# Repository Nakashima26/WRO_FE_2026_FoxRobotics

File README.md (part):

# WRO 2026 — Future Engineers | Self-Driving Car

> **Team:** FoxRobotics
> **| Members:** Erick Blanco · Jesse Banda · César Emiliano Ahumada
> **| Coach:** Daniel Millan
> **| Country / Region:** México — Baja California
> **| Season:** 2026

---

## Table of Contents

1. [Vehicle Overview](#1-vehicle-overview)
   - [1.1 Design goals](#11-design-goals) · [1.2 Bill of Materials](#12-bill-of-materials) · [1.3 What changed in v2](#13-what-changed-for-the-international-final-v2)
2. [Mechanical Design & Mobility](#2-mechanical-design--mobility)
   - [2.1 Chassis selection](#21-chassis-selection) · [2.2 Wheels](#22-wheels) · [2.3 Drive system (torque vs. speed)](#23-drive-system-torque-vs-speed-analysis) · [2.4 Steering](#24-steering--rack-and-pinion-with-ackermann-geometry) · [2.5 Custom parts & assembly](#25-custom-parts--assembly) · [2.6 v2 chassis](#26-v2-chassis--shorter-car-pi-on-top)
3. [Power Architecture & Sensors](#3-power-architecture--sensors)
   - [3.1 Power budget](#31-power-budget) · [3.2 Sensor selection and placement](#32-sensor-selection-and-placement) · [3.3 PCB & wiring](#33-pcb--wiring) · [3.4 Raspberry Pi 5](#34-main-computer--raspberry-pi-5-v2)
4. [Software Architecture](#4-software-architecture)
   - [4.1 System overview](#41-system-overview--two-controllers-one-link) · [4.2 Inter-controller protocol ("V2")](#42-inter-controller-protocol-v2) · [4.3 Vision pipeline](#43-vision-pipeline-raspberry-pi--pure_pursuit) · [4.4 Obstacle handling](#44-obstacle-handling-obstacle-challenge) · [4.5 ESP32 state machine](#45-esp32-finite-state-machine-srcesp32purepursuitpurepursuitino) · [4.6 Cascade PID](#46-cascade-pid-always-running-underneath) · [4.7 Startup handshake](#47-startup-handshake) · [4.8 Development status](#48-development-status) · [4.9 Route mode (v2)](#49-route-mode-v2--a-planned-route-instead-of-reactive-steering)
5. [Systemic Thinking & Engineering Decisions](#5-systemic-thinking--engineering-decisions)
   - [5.0 Design constraints](#50-design-constraints) · [5.1 Subsystem interaction map](#51-subsystem-interaction-map) · [5.2 Key engineering trade-offs](#52-key-engineering-trade-offs) · [5.3 Iteration log](#53-iteration-log) · [5.4 Risk analysis](#54-risk-analysis) · [5.5 Failure & Incident log](#55-failure--incident-log)
6. [Testing & Validation](#6-testing--validation)
   - [6.1 How we test](#61-how-we-test) · [6.2 Results to date](#62-results-to-date) · [6.3 Validation matrix](#63-validation-matrix) · [6.4 Pre-run checklist](#64-pre-run-checklist-each-venue) · [6.5 Milestones](#65-milestones) · [6.6 Releases](#66-releases)
7. [How to Build & Run](#7-how-to-build--run)
   - [7.1 Hardware](#71-hardware-requirements) · [7.2 ESP32 firmware](#72-esp32-firmware) · [7.3 Raspberry Pi software](#73-raspberry-pi-software) · [7.4 Calibration](#74-calibration-before-each-venue) · [7.5 Run](#75-run) · [7.6 Autostart & deployment](#76-autostart--deployment)
8. [Repository Structure](#8-repository-structure)
9. [Videos](#9-videos)
10. [Photos](#10-photos)

**Companion document:** [Engineering Journal](ENGINEERING_JOURNAL.md) — the dated, phase-by-phase build log, from the pre-repo design work through today, tied to commits. [§5.3 Iteration log](#53-iteration-log) and [§6.5 Milestones](#65-milestones) are the thematic views of the same history.

---

# 1. Vehicle Overview

Our vehicle is a custom-built autonomous car for the WRO 2026 Future Engineers — Self-Driving Cars challenge. It completes 3 laps around a randomized track, and in the Obstacle Challenge it also detects and correctly passes coloured traffic-sign pillars (**red → keep the pillar on the car's left / pass on its right; green → keep it on the right / pass on its left**) before parking at the end.

The car uses **two controllers working together**: a Raspberry Pi runs the camera vision pipeline (a Raspberry Pi 4 at the national final, a Raspberry Pi 5 for the international final) and the high-level path planner (Pure Pursuit), and an ESP32 runs the real-time control loop, the state machine and all the actuators. They talk over a UART link with a small line-based protocol ("V2"). This split is the central architectural decision of the project and is explained in [Section 4](#4-software-architecture) and [Section 5](#5-systemic-thinking--engineering-decisions).

**Key specifications:**

| Parameter | Value |
|---|---|
| Dimensions | v1: 210 × 140 × 80 mm body, ≈240 mm overall with the extension added to drive out of the parking lot · v2: ≈170 × 130 × 110 mm (168.7 × 128 mm in CAD; height includes the camera ribbon over the top, §2.6) |
| Weight | 564 g |
| Drive type | Rear-wheel drive (RWD) |
| Steering | Ackermann rack-and-pinion, SG90 servo — v2: 53° inner / 37° outer wheel at full lock, ~106% Ackermann (§2.4) |
| High-level controller | Raspberry Pi 5, 16 GB + Active Cooler (vision + Pure Pursuit) — Raspberry Pi 4 Model B until the national final (§3.4) |
| Real-time controller | ESP32 DevKit (FSM, PID, motor & sensor I/O) |
| Inter-controller link | UART @ 115200 baud, line protocol "V2" (see §4.2) |
| Vision | Raspberry Pi Camera, NoIR wide-angle lens (FOV ≈ 120°), processed at 640 × 480; custom lens-shading calibration on the Pi 5 (ERR-03) |
| Distance sensors | HC-SR04 (5V) × 3 — left, right, front — via 5V↔3.3V level shifter · v2: + VL53L1X ToF × 4, in integration (§3.2) |
| IMU | MPU-6050 (gyroscope + accelerometer) · v2: BNO085 with on-chip sensor fusion, in integration (§3.2) |
| Drive motor | v1: N20 DC gear motor (50:1) · v2: Pololu 50:1 12 V gear motor **with encoder** · + 2:1 stage → 100:1 total |
| Motor driver | TB6612FNG |
| Battery | 3S LiPo 11.1 V 2200 mAh |
| Logic power | MINI560 step-down, 5 V |

## 1.1 Design goals

One reliable vehicle that finishes **both** challenges — scoring for completing three laps consistently over completing them fast. Everything below follows from that.

- **Fixed architecture from day one: Raspberry Pi 4 + ESP32.** The Pi does *all* image processing and vision; the ESP32 does *all* peripheral I/O — both sensing and actuation. This split was decided before the first line of code and never revisited.
- **Small footprint for maneuverability.** Comfortably inside the rulebook envelope with ~10 cm of margin on width and length — the car is ≈ 20 × 10 cm, deliberately smaller than the limit so it has room to maneuver in the obstacle field.
- **Mechanically extensible.** The chassis and the PCB were designed so components could be added later without a redesign. This paid off directly: the front ultrasonic — added for the obstacle-round segmented turn (see [§4.5](#45-esp32-finite-state-machine-srcesp32purepursuitpurepursuitino)) — went from idea to mounted-and-wired in under 30 minutes because both the chassis and the PCB already had the space and a spare header.
- **Tight-turn capable.** Rack-and-pinion steering driving both wheels symmetrically ([§2.4](#24-steering--rack-and-pinion-with-ackermann-geometry)) so the car can take the obstacle-round corners without a multi-point turn.
- **Room for a printed differential** so the rear wheels can turn at different speeds through a corner without scrub.
- **Electronics-first packaging.** The chassis was sized around the electronics — the Raspberry Pi 4 above all — and the PCB was then laid out to fit the finished mechanical model, not the other way around.

## 1.2 Bill of Materials

### Custom Manufactured Parts

| ID | Component | Description | Quantity | Supplier | Approximate Cost |
|---|---|---|---|---|---|
| 1 | BaseChasis | Main body of the vehicle. | 1 | Custom made, 3D printed | 1.6 USD |
| 2 | TopShell | Upper part of the vehicle. | 1 | Custom made, 3D printed | 1 USD |
| 3 | Cremallera | Rack used for steering. | 1 | Custom made, 3D printed | 0.1 USD |
| 4 | ServoGearDirection | Pinion for the steering system, directly connected to the servo. | 1 | Custom made, 3D printed | 0.5 USD |
| 5 | LinkageDirection | Linkage between the rack and steering knuckle. | 2 | Custom made, 3D printed | 0.05 USD |
| 6 | SteeringKnuckle | Allows lateral wheel movement for steering. | 2 | Custom made, 3D printed | 0.15 USD |
| 7 | DCsupport | Holds the DC motor in place. | 1 | Custom made, 3D printed | 0.05 USD |
| 8 | RingDifferential | Main driven gear of the differential that transfers power to the axle assembly. | 1 | Custom made, 3D printed | 0.25 USD |
| 9 | PlanetDifferential | Allows torque distribution between both wheels while enabling different wheel speeds during turns. | 2 | Custom made, 3D printed | 0.1 USD |
| 10 | PinionDifferential | Transfers rotational motion from the motor to the differential gear system. | 1 | Custom made, 3D printed | 0.1 USD |
| 11 | SunDifferential | Transfers torque from the differential gears to the wheel axle. | 2 | Custom made, 3D printed | 0.1 USD |
| 12 | CameraBase | Holds the camera frame in place. | 1 | Custom made, 3D printed | 0.1 USD |
| 13 | CameraBack | Rear section of the camera frame. Connects to the CameraBase. | 1 | Custom made, 3D printed | 0.1 USD |
| 14 | CameraFront | Camera frame. | 1 | Custom made, 3D printed | 0.2 USD |
| 15 | UltrasonicSupport | Holds an ultrasonic sensor in place (used for the left, right and front sensors). | 3 | Custom made, 3D printed | 0.3 USD |

---

### LEGO Components

| ID | Component | Description | Quantity | Supplier | Approximate Cost |
|---|---|---|---|---|---|
| 16 | Lego 6135494 | Front wheel axle. | 2 | LEGO | 0.8 USD |
| 17 | Lego 4535768 | Rear wheel axle. | 2 | LEGO | 1 USD |
| 18 | Lego 6121485 | Reduces friction on the rear wheels. | 2 | LEGO | 0.4 USD |
| 19 | Lego 4299389 | Rim for rear wheels. | 2 | LEGO | 1.2 USD |
| 20 | Lego 4184286 | Tires for rear wheels. | 2 | LEGO | 3.5 USD |
| 21 | Lego 6251174 | Rim for front wheels. | 2 | LEGO | 1.2 USD |
| 22 | Lego 6182551 | Tires for front wheels. | 2 | LEGO | 3.82 USD |

---

### Electronics

| ID | Component | Description | Quantity | Supplier | Approximate Cost |
|---|---|---|---|---|---|
| 23 | ESP32 | Real-time controller: sensor I/O, cascade PID, finite state machine, actuator PWM. | 1 | Unit Electronics | 8 USD |
| 24 | Raspberry Pi 5 (16 GB) + Active Cooler + M.2 HAT+ | High-level controller: computer vision and Pure Pursuit path planning. Replaced the Raspberry Pi 4 (60 USD) after the national final; price includes taxes and shipping. | 1 | Official reseller | 410 USD |
| 25 | Mini560 5V | Step-down regulators. v2 uses two: one only for the Raspberry Pi 5, one for the ESP32, servo and sensors (v1 had one for everything). | 2 | Amazon | 12 USD |
| 26 | BNO085 | 9-axis IMU with on-chip sensor fusion (heading at 100 Hz). Replaced the MPU-6050 (3 USD) in v2. | 1 | Local purchase | 27 USD (500 MXN) |
| 38 | VL53L1X | Laser time-of-flight distance sensors — front, left, right and rear (v2). | 4 | Local purchase | 27 USD total (500 MXN) |
| 27 | HC-SR04 | Ultrasonic distance sensors — left, right (wall following) and front (obstacle-round cornering). | 3 | Unit Electronics | 10.5 USD |
| 28 | Level Shifter | Logic-level converter for the 5 V HC-SR04 echo lines into the 3.3 V ESP32. | 1 | Unit Electronics | 7 USD |
| 29 | Driver TB6612FNG | Motor driver controlling speed and direction of the DC drive motor. | 1 | Unit Electronics | 5 USD |
| 30 | RaspiCamera V2 | Camera module used for computer vision. Came with both ribbon cables: 15-pin for the Raspberry Pi 4 and 22-to-15-pin for the Raspberry Pi 5. | 1 | Amazon | 10 USD |
| 31 | Custom PCB | Power distribution and all signal connections. v1: single board (5 USD); v2: two-floor board, in design — price pending. | 1 | JLCPCB | 5 USD (v1) |

---

### Power System

| ID | Component | Description | Quantity | Supplier | Approximate Cost |
|---|---|---|---|---|---|
| 32 | Ovonic 2200mAh 3S | 3-cell LiPo battery powering the robot's electronics and drive system. | 1 | E-Bay | 13 USD |

---

### Actuators

| ID | Component | Description | Quantity | Supplier | Approximate Cost |
|---|---|---|---|---|---|
| 33 | Pololu 50:1 12 V gear motor with encoder | Drive motor; the encoder measures speed and distance. Replaced the N20 50:1 (6 USD) in v2. | 1 | Pololu | 20 USD |
| 34 | SG90 Servo | Micro servo motor used for steering control. | 1 | Unit Electronics | 6 USD |

---

### Fasteners

| ID | Component | Description | Quantity | Supplier | Approximate Cost |
|---|---|---|---|---|---|
| 35 | M3 Screws | Used for structural assembly and component mounting. | 23 | Local Hardware Store | 1 USD |
| 36 | M3 Nuts | Used to secure structural and electronic components. | 1 | Local Hardware Store | 0.05 USD |
| 37 | M2 Nuts | Used to secure servo motor and servo pinion | 3 | Local Hardware Store | 0.15 USD |

### Total Estimated Cost

| Version | Total |
|---|---|
| v1 — national final | ~155 USD |
| v2 — international final | **~576 USD** + v2 PCB (pending) |

**Where the increase comes from:** +410 USD Raspberry Pi 5 bundle, +27 BNO085, +27 VL53L1X ×4, +20 encoder motor, +6 second regulator; −69 USD for the parts that left the car (Raspberry Pi 4, MPU-6050, N20). About 85% of the increase is the Raspberry Pi 5, justified by the profiling in [§3.4](#34-main-computer--raspberry-pi-5-v2): 40 fps vs ~15 fps, no thermal throttling.

## 1.3 What changed for the international final (v2)

After winning the national final (2026-09-19, release [`v1.0-nacional`](docs/releases.md)) we reworked the parts of the car that were limiting it. Each change has its own section with the numbers behind it.

| Area | v1 (national final) | v2 | Why | Details |
|---|---|---|---|---|
| Steering geometry | Anti-Ackermann: the outer wheel steered *more* than the inner one (39.5° inner / 42.8° outer) | Ackermann corrected: rack joints 43 → 47 mm apart, tie rods 18.13 mm | Both front wheels now roll around the same turning center instead of fighting each other | [2.4](#24-steering--rack-and-pinion-with-ackermann-geometry) |
| Steering pinion | Module 1, 14 teeth | Module 1, **19 teeth**; servo moved 2.5 mm away from the rack | Same servo travel moves the rack 36% further: ~37° → **53°** on the inner wheel (measured in CAD) | [2.4](#24-steering--rack-and-pinion-with-ackermann-geometry) |
| Main computer | Raspberry Pi 4 | **Raspberry Pi 5, 16 GB** + Active Cooler | The Pi 4 was compute-bound at 14–18 fps and hit thermal throttling at 84 °C; the Pi 5 runs the same pipeline at ~40 fps at 52 °C | [3.4](#34-main-computer--raspberry-pi-5-v2) |
| Chassis layout | ≈24 cm long; Raspberry Pi enclosed in the center; motor perpendicular to the rear axle (bevel gears) | **≈17 cm long**; battery in the center where the Pi was; Pi 5 on top, open to the air; motor parallel to the axle (spur gears, same 2:1) | Tighter turns and more room to dodge and park; the enclosed Pi overheated (84 °C, throttling) | [2.6](#26-v2-chassis--shorter-car-pi-on-top) |
| Distance sensing | 3 × HC-SR04 only | 3 × HC-SR04 **+** 4 × **VL53L1X** ToF (front, left, right, rear), cross-checked against each other | Each sensor type fails differently against the black walls: the ultrasonic gives phantom echoes, the ToF can lose a dark wall. Using both lets each one veto the other's known failure | [3.2](#why-both-ultrasonic-and-tof) |
| Drive motor | N20 50:1, open-loop | **Pololu 50:1 with encoder** (mounted; speed loop pending) | Maneuvers changed with battery voltage; the encoder gives measured speed and distance | [2.6](#26-v2-chassis--shorter-car-pi-on-top) |
| IMU | MPU-6050, gyro rate integrated on the ESP32 | **BNO085**, fused heading computed on the sensor (UART-RVC, 100 Hz) | Integrated heading was 6.5% low over a run and carried a −7.5° bias after every corner maneuver | [3.2](#bno085-imu-v2-in-integration) |
| Power | One 5 V regulator for everything | **Two** regulators: one only for the Raspberry Pi 5 | Servo current spikes must not sag the Pi's supply; the Pi 5 draws more | [3.1](#v2-power-budget) |
| PCB | One board | **Two-floor** board: power floor + logic floor (in design) | The shorter chassis has less area, and four ToF + BNO085 need new connectors | [3.3](#v2-pcb--two-floor-board-in-design) |
| Camera color | Fixed white-balance gains only (Pi 4) | Lens-shading table calibrated for our lens + gains, as a project tuning file | The new image processor of the Pi 5 showed a magenta ring at the frame edges, close to the pink parking walls and red pillars | [ERR-03](#err-03--wide-angle-noir-lens-put-a-red-cast-on-every-frame) |
| Documentation | One README | + [releases](docs/releases.md), [test record](docs/testing.md), [engineering log](docs/engineering-log.md) (ERR-10 onward) | One release per event; every failure tied to a run number and a commit | §6 |

---

# 2. Mechanical Design & Mobility

### 2.1 Chassis selection

The chassis was designed from scratch to fit all the components we needed for competition. We printed it in red and black SUNLU PLA on a Bambu Lab A1, keeping the structure as light as possible without sacrificing the rigidity the drivetrain and electronics require.

For wheel transmission shafts, we used LEGO axles throughout: part 6135494 for the front and part 4535768 for the rear. This wasn't an aesthetic choice — LEGO axles have much better dimensional consistency than fully printed shafts, which flex under load and cause alignment issues. We also added LEGO bushings (6121485) to the rear axle to cut down on friction between moving parts.

| Component   | Material / Part | Purpose                 |
| ----------- | --------------- | ----------------------- |
| Chassis     | SUNLU PLA       | Main robot structure    |
| Front Axles | LEGO 6135494    | Power transmission      |
| Rear Axles  | LEGO 4535768    | Rear drivetrain support |
| Bushings    | LEGO 6121485    | Friction reduction      |
| Printer     | Bambu Lab A1    | Manufacturing process   |

We used PLA because it prints fast, doesn't warp like ABS, and is stiff enough for indoor competition conditions. PETG has better impact resistance and ABS handles heat better, but neither of those properties matters much for a robot running on a flat mat indoors. What did matter was being able to iterate quickly and get consistent parts, and PLA delivered on both.

### 2.2 Wheels

We tested several wheel options before settling on LEGO parts. The rear wheels use rim 4299389 with tire 4184286, and the front uses rim 6251174 with tire 6182551. Both have a 43 mm outer diameter, which keeps the ride height even front to rear.

Since the drivetrain already uses LEGO axles, LEGO-compatible rims were the obvious fit — they mount directly without adapters, which removes a potential source of wobble at the wheel interface.

The 43 mm diameter was also validated against our motor RPM target. At our gear ratio, this diameter puts normal operation in the 40–70% PWM range, which gives us enough resolution for smooth speed control. A noticeably larger wheel would push operating duty cycles above 85% and compress the usable throttle range.

We ran the car at full throttle on the competition mat surface and saw no detectable slip at the rear. The LEGO rubber compound grips the white matte WRO field without any prep needed.

### 2.3 Drive system (torque vs. speed analysis)

The main drive is an N20 DC motor with a 50:1 internal gearbox — compact at 12 × 10 × 26 mm and still enough torque for a ~1.5 kg vehicle. Between the motor output shaft and the differential, we added a 2:1 LEGO gear stage, bringing the total drivetrain reduction to **100:1** and estimated rear axle torque to about 1.76 kg·cm.

**Why 100:1 and not just 50:1?**

We ran the 50:1 configuration first. It was faster, but corner exits were inconsistent — the rear wheels would occasionally lose traction under acceleration, causing yaw disturbances the PID couldn't fully catch. At 100:1, top speed dropped but torque delivery became smooth and predictable all the way through the speed range. Corner exits became repeatable, which turned out to be a prerequisite for reliable PID tuning.

The ratio also keeps the motor in its efficient RPM band during most of the run, which matters because the motor shares a power source with the logic rail.

Official time at the national final, Open Challenge round 1: **57.455 s** for the three laps, driven at a conservative speed for reliability. v2 spends that headroom with a planned route and a speed profile ([§4.9](#49-route-mode-v2--a-planned-route-instead-of-reactive-steering)).

**The takeaway:** we prioritized consistency over raw speed. A robot that reliably finishes 3 laps scores more than one that's faster but unpredictable.

### 2.4 Steering — rack-and-pinion with Ackermann geometry

Steering is controlled by an SG90 servo connected to both front knuckles through a rack-and-pinion mechanism with symmetric tie rods.

**Mechanism specs (v1, national final):**

| Parameter | Value |
|---|---|
| Servo | SG90 (0°–180° range) |
| Firmware straight-ahead trim | 80° (servo-horn spline offset; `centroServo` in firmware) |
| Pinion | Module 1, 14 teeth |
| Pinion pitch diameter | 14 mm (dp = m × z = 1 × 14) |
| Pinion outer diameter | 16 mm (dp + 2×addendum = 14 + 2) |
| Rack | Module 1, 11 teeth, 27.5 mm total travel |
| Rack displacement per servo degree | 0.1222 mm/° |
| Transmission ratio | 2.50° servo : 1° wheel |
| Geometric wheel steering range | ±43° from center |
| Firmware-clamped servo command | 20°–150° (≈ ±35° usable at the wheel) |

**Kinematic analysis:**

The 14 mm pitch diameter gives a pitch circumference of 43.98 mm. Each degree of servo rotation moves the rack 0.1222 mm. At 90° per side from center, the rack travels 11.00 mm per side — producing ±43° at the front wheels.

The outer diameter of 16 mm confirms the module (d_outer = dp + 2×m = 14 + 2 = 16 mm).

The 2.50:1 ratio reduces steering sensitivity at the wheel, which gives the inner control loop finer resolution at its update rate. A lower ratio would make steering response too abrupt.

The firmware never commands the full mechanical range: `escribirServo()` is clamped to 20°–150° (about ±35° at the wheel) so a saturated control output can't drive the rack into its physical end stop. That still clears the tightest Open-Challenge corridor (600 mm) and the maneuvering the Obstacle Challenge needs.

**Why rack-and-pinion over a direct servo arm?**

A direct arm only controls one wheel directly. The opposite knuckle, linked by a fixed-length tie rod, gets an angle that's geometrically correct only at center — producing toe error everywhere else. The rack pushes both tie rods symmetrically, so both wheels get the right angle at every steering position. Combined with the Ackermann geometry of the knuckles, each wheel tracks its own correct turning radius. No lateral scrub, and steering response is linear across the full range.

#### v2 redesign (October 2026) — Ackermann fix and a bigger pinion

In v2 we redesigned this mechanism because of two problems: the geometry was **anti-Ackermann**, and the car **could not turn tightly enough**. We simulated the linkage in Python with the exact CAD dimensions (the model matched the CAD within ~1°) before reprinting anything.

**Geometry reference** (top view, wheels straight, measured in SolidWorks):

| Parameter | Value |
|---|---|
| Kingpin track T (distance between the two knuckle pivots) | 60 mm |
| Wheelbase L (front kingpin line → rear axle) | 112.85 mm |
| Knuckle steering arm (pivot → tie-rod joint) | 12.49 mm, pointing ~43° outward and backward |
| Rack joints behind the kingpin line | 18.94 mm |
| Servo swing actually used | ±71° (measured from the rack travel, not the nominal ±90°) |

##### Problem 1 — anti-Ackermann (fixed)

In a turn, the inner wheel follows a smaller circle than the outer wheel, so it must steer **more**. Correct (100%) Ackermann is reached when

  **cot(δ_outer) − cot(δ_inner) = T / L = 0.532**

and the axis lines of both front wheels cross on the rear axle line.

In v1 the rack joints were only 28.5 mm apart with 26 mm tie rods. We simulated the linkage in Python with the exact CAD dimensions, and the model matched the CAD within ~1°. At full travel the car steered **39.5° on the inner wheel and 42.8° on the outer wheel**: the outer wheel was steering *more* than the inner one. The two front wheels were trying to turn around different centers, so one of them always dragged sideways. That cost traction and current in every corner, and the car turned wider than the servo command implied.

Because the knuckles had to stay as they were (a new knuckle means a new arm, and the rack position is fixed by the chassis), we only changed **the spacing between the rack joints** and **the tie-rod length**. Those two values must change together: for the wheels to point straight with the rack centered, the tie rod must be

  **linkage = √( (38.66 − spacing/2)² + 9.94² )**  (mm, center to center)

| Rack joint spacing | Tie rod | Ackermann at 30° | 40° | 45° | 50° | 55° |
|---|---|---|---|---|---|---|
| 28.5 (v1) | 26.0 | anti-Ackermann | | | | |
| 43.0 (intermediate) | 19.83 | 51% | 62% | 69% | 76% | 84% |
| **47.0 (v2)** | **18.13** | 76% | **89%** | **95%** | **102%** | 110% |
| 50.0 | 16.89 | 99% | 111% | 117% | 124% | 131% |

*(Percentage = how much of the ideal inner/outer difference the linkage achieves. Below 100% the outer wheel steers slightly too much; above 100% it steers too little.)*

**Why 47 mm:** with a fixed knuckle, Ackermann cannot be exact over the whole range, because the percentage grows as the wheels turn. We chose the spacing that is closest to 100% in the 40°–50° range, which is where the car actually turns at corners and during parking. At small angles the error is under 0.7°, so it does not matter there. Each 0.1 mm of tie-rod error toes a wheel by ~0.5°, so the printed linkages are trimmed in 0.05–0.1 mm steps until the wheels are straight.

##### Problem 2 — turning radius (bigger pinion)

The steering angle depends almost only on **how far the rack moves**, and with the v1 pinion that was **±8.7 mm**: only ~37° on the inner wheel. We looked at three options: shorter knuckle arms, moving the rack, and a bigger pinion. The bigger pinion was the only one that needed no new chassis or knuckles.

| | v1 | **v2** |
|---|---|---|
| Pinion | Module 1, 14 teeth | **Module 1, 19 teeth** (20° pressure angle) |
| Pitch / outer diameter | 14 / 16 mm | **19 / 21 mm** |
| Rack travel per servo degree | 0.122 mm/° | **0.166 mm/°** |
| Rack travel at ±71° servo | ±8.7 mm | **±11.8 mm** |
| Inner / outer wheel at full lock | ~37° / ~32° (with 43 mm spacing) | **53.1° / 37.0°** (measured in the CAD assembly; the linkage model predicted ~50° / ~37°) |
| Turning radius at the rear-axle center (L / tan δ_inner + T/2) | ~208 mm (v1: 147 mm wheelbase, 39.5°) | **~115 mm** (v2: 113 mm wheelbase) — −45% |
| Ackermann at full lock | anti-Ackermann | **~106%** (ideal outer for 53.1° inner = 37.9°, measured 37.0°) |

- **Servo position.** The pitch radius grows from 7 to 9.5 mm, so the servo axis moved **2.5 mm away from the rack** with a spacer on its mount. The rack and the tie-rod joints stay at the same height, so the linkage geometry above is not affected.
- **Pinion profile.** We generated the involute tooth profile with our own script ([`Mecanica/Engranes/gen_pinon.py`](Mecanica/Engranes/gen_pinon.py)) and exported it as a single closed DXF contour that we extrude in SolidWorks. It includes 0.10 mm of backlash for 3D printing.
- **Toggle limit.** The linkage would lock (arm and tie rod aligned) at around 16 mm of rack travel. If the servo ever reached a true ±90°, the 19-tooth pinion could push the rack to ±14.9 mm. The intended mechanical stop is the knuckle touching the chassis before that point, and the servo output is also clamped in software.
- **Servo load.** The bigger pinion needs ~1.36× more servo torque for the same rack force. It also loses some angular resolution, which is still fine for an SG90 in a 0.5 kg car. The servo must not be left stalled against the stop, because it heats up and drags down the 5 V rail.

**Servo calibration.** The servo-to-wheel relation is no longer linear: near full lock the wheels turn faster per servo degree. The servo map and the steering gains in the ESP32 firmware are recalibrated on the assembled car (pending).

### 2.5 Custom parts & assembly

Every structural part is 3D-printed in SUNLU PLA on a Bambu Lab A1. The mechanical model was built first; the PCB was then laid out to fit it. Editable SolidWorks parts are in [`models/CAD/`](models/CAD/), printable meshes in [`models/STL/`](models/STL/), isometric renders in [`models/renders/`](models/renders/).

| Render | Part | Function / design note |
|---|---|---|
|  | **BaseChasis** | Main structure. Sized around the electronics (Raspberry Pi 4 first); carries the PCB, steering, drivetrain and every sensor mount. |
|  | **TopShell** | Top cover — closes the electronics bay and protects the wiring. |
|  | **ServoGearDirection** | Pinion pressed onto the SG90 output shaft — module 1, 14 teeth (19 teeth in v2, [§2.4](#24-steering--rack-and-pinion-with-ackermann-geometry); profile generated by [`Mecanica/Engranes/gen_pinon.py`](Mecanica/Engranes/gen_pinon.py)). |
|  | **Cremallera** (rack) | Module 1, 11 teeth, 27.5 mm travel. Converts servo rotation into lateral travel for the tie rods. |
|  | **LinkageDirection** ×2 | Tie rods from the rack ends to the steering knuckles — symmetric, so both wheels get the correct angle at every rack position. |
|  | **SteeringKnuckle** ×2 | Front-wheel pivots; their geometry sets the Ackermann steering angles. |
|  | **Differential** (Ring / Planet ×2 / Pinion / Sun) | Printed open differential — lets the rear wheels turn at different speeds through a corner. |
|  | **DCsupport** | Mounts the N20 gear motor to the chassis. |
|  | **UltrasonicSupport** ×3 | Two identical side mounts; one slightly smaller front mount, added later for the obstacle-round segmented turn. |
|  | **CameraHold** | Structure in charge of holding the camera. Sets the fixed ~20° downward tilt the BEV homography is calibrated against ([§3.2](#32-sensor-selection-and-placement)). |

#### Assembly order

1. **Chassis base** — the reference part everything mounts to.
2. **Steering** — press the pinion onto the servo and seat the servo in the chassis; slide in the rack; link each rack end to a SteeringKnuckle with a LinkageDirection tie rod; fit the knuckles and the front LEGO axles.
3. **Drivetrain** — N20 motor into the DCsupport; assemble the printed differential; rear LEGO axles with bushings.
4. **Sensor mounts** — the two side UltrasonicSupports (identical) and the smaller front one; the camera cage (base + back + front) with the camera.
5. **Electronics** — PCB onto the chassis bosses; wire the Pi 4, ESP32, the three HC-SR04 (through the level shifter), the MPU-6050, the TB6612 + motor, the servo, and the start button + status LED.
6. **TopShell** — close the bay.

All fasteners are M3 (M2 nuts on the servo horn and pinion).

### 2.6 v2 chassis — shorter car, Pi on top

*Status: designed in SolidWorks, being printed. Final dimensions and weight will be measured on the printed car.*

For the international final we rebuilt the chassis around two problems we kept seeing at the national final:

1. **The car was long for the obstacle field.** The body was 210 mm, but it reached ≈24 cm overall with an extension we added so the car could drive out of the parking lot comfortably. At that length every dodge swept a lot of floor, and the parking maneuver had little room in the lot.
2. **The Raspberry Pi overheated.** It sat enclosed in the middle of the chassis. With the remote-view client running it reached **84 °C** and throttled its CPU ([ERR-27](docs/engineering-log.md#err-27--the-remote-desktop-client-overheated-the-pi-4)), which lowered the vision frame rate.

**What we changed**

| Change | How | Why |
|---|---|---|
| **Motor parallel to the rear axle** | The drive motor now lies along the axle and drives the differential through **spur gears** (module 1, 15-tooth pinion on the motor's D-shaft, 30-tooth ring on the differential) instead of the perpendicular bevel pair | A motor perpendicular to the axle adds its whole length to the car. Lying along the axle, it adds almost nothing. |
| **Battery in the center** | The 3S pack sits crosswise in a side-loading tunnel, in the space the Raspberry Pi used to take | The heaviest part ends up in the middle and low, which balances the load front to rear. The side tunnel makes battery swaps quick. |
| **Raspberry Pi 5 on top** | The Pi moves from the enclosed center bay to the top of the car | The Active Cooler needs free air. Enclosed, the Pi recirculated its own hot air. On top, it also stays reachable for the camera cable and the SSD. |
| **Encoder motor** | Pololu 50:1 12 V gear motor with a quadrature encoder replaces the plain N20; same 50:1 ratio | Motor speed is open-loop today, so maneuvers change with battery voltage ([ERR-11](docs/engineering-log.md#err-11--a-fresh-battery-over-rotates-the-dodges)). The encoder lets the ESP32 hold a speed and measure distance, as the rules' reference build suggests. *Mounted; firmware integration pending.* |
| **Overall length ≈24 cm → ≈17 cm** (width 128 mm) | Result of the changes above | See below |

**Why a shorter car turns tighter.** For Ackermann steering, the radius of the path at the center of the rear axle is

  **R = L / tan(δ_inner) + T/2**

where L is the wheelbase and T the kingpin track (60 mm). Shortening L shrinks R directly, at the same steering angle. With the v2 steering (53° inner wheel, [§2.4](#24-steering--rack-and-pinion-with-ackermann-geometry)) and the v2 wheelbase of **≈113 mm** (CAD), R ≈ **115 mm**. The v1 car had a wheelbase of ≈147 mm (measured) and ~40° of steering, so R ≈ **208 mm**. The turning radius is therefore **≈45% smaller**: about half from the shorter wheelbase, about half from the bigger steering angle. A smaller radius means a dodge needs less lateral room, the stop-and-turn corner maneuver needs less space ahead of the front wall, and the car fits the parking lot with more margin.

**The drivetrain keeps its ratio.** The old bevel pair was 36:18 = 2:1, and the new spur pair is 30:15 = 2:1. The total reduction stays at **100:1**, so the torque and speed analysis of [§2.3](#23-drive-system-torque-vs-speed-analysis) still holds. Spur gears are also easier to print accurately and to align than bevel gears. We checked the tooth strength with the Lewis bending equation (8 mm face, at the N20's stall torque): ≈5.7 MPa, roughly 9× below the strength of printed PLA. It is re-checked with the stall torque of the encoder motor. The gear center distance is designed at 22.6–22.7 mm (22.5 mm nominal) to leave printing clearance. The involute profiles are generated by our own script and exported as DXF; SolidWorks Standard has no gear generator.

**What stayed about the same, on purpose:** the height of the chassis, for stability in fast turns (the v2 car is ≈110 mm tall, but only the camera ribbon over the top reaches that);  the LEGO axles and wheels ([§2.1](#21-chassis-selection), [§2.2](#22-wheels)); and the camera height and angle, so the bird's-eye-view calibration concept carries over (it is re-calibrated on the new mount).

---

# 3. Power Architecture & Sensors

### 3.1 Power budget

The whole vehicle runs off an Ovonic 2200mAh 3S LiPo. Power splits two ways: the motor driver takes battery voltage directly for the DC motor, and everything else goes through a MINI560 step-down converter producing a stable 5V at up to 5A.

| Rail | Source | Consumers | Max Current Draw |
|---|---|---|---|
| 5V Logic | MINI560 Step-Down Converter | Raspberry Pi 4 + RaspiCam V2, ESP32, HC-SR04 ×3, MPU6050, SG90 | ~4.0 A |
| Battery / Main Power | Ovonic 2200mAh 3S LiPo | Entire vehicle power distribution | ~35 A discharge capability |
| Motor Power | Motor Driver directly from 3S LiPo | DC drive motor | ~1.6 A peak |
| 3.3V Internal | ESP32 internal regulator | I²C communication and internal ESP32 logic, Level Shifter | ~200 mA |

The Ovonic battery is rated 120C continuous, which is theoretically 264 A. We're drawing about 4.5 A peak — under 2% of its discharge capability. There's no shortage of headroom here.

The Raspberry Pi and the ESP32 share the 5 V rail but the DC motor is fed straight from the battery through the TB6612FNG, so stall-current spikes on the motor never sag the logic supply.

#### v2 power budget

*Design values from the component datasheets and the Raspberry Pi documentation. Each rail will be measured with an inline meter on the assembled v2 car, and the measured values will replace these.*

The Raspberry Pi 5 draws more than the Pi 4 and is sensitive to voltage drops: when its supply sags it throttles the CPU, which directly lowers the vision frame rate. We already saw this on the Pi 4 when it was fed through Dupont jumpers (`throttled=0x50005`, CPU down to 600 MHz, [ERR-08](#err-08--raspberry-pi-undervoltage-from-undersized-power-wiring)). v2 therefore has **two 5 V regulators**: one only for the Raspberry Pi 5, and one for everything else. The servo's current spikes can no longer pull down the Pi's supply.

| Rail | Load | Typical | Design peak | Basis |
|---|---|---:|---:|---|
| **5 V-A** (Mini560 #1, 5 A) | Raspberry Pi 5 under vision load | 1.5 A | 2.5 A | 0.8 A bare-board active (Raspberry Pi docs) + 4 cores busy; peak covers load spikes |
| | Camera v2 | 0.25 A | 0.25 A | Camera module figure |
| | Active Cooler fan | 0.05 A | 0.1 A | Fan at full speed above 75 °C |
| | **Rail total** | **1.8 A** | **2.85 A** | 57% of the regulator's 5 A at peak |
| **5 V-B** (Mini560 #2, 5 A) | ESP32 (radio off) | 0.08 A | 0.25 A | Datasheet |
| | SG90 servo | 0.25 A | 0.70 A | Running current; peak = stall |
| | HC-SR04 × 3 | 0.045 A | 0.045 A | 15 mA each |
| | VL53L1X × 4 | 0.08 A | 0.16 A | ~20 mA each ranging, 40 mA peak |
| | BNO085 | 0.013 A | 0.013 A | Datasheet operating figure |
| | **Rail total** | **0.47 A** | **1.17 A** | 23% of the regulator at peak |
| **Battery 11.1 V** | Drive motor via TB6612 | — | 1.6 A | Peak measured on v1 (N20); to be re-measured with the encoder motor |
| **5 V-B** | Motor encoder | 0.01 A | 0.01 A | Hall-effect encoder |

**Battery current.** With ~90% regulator efficiency, the two 5 V rails at design peak draw 5 V × (2.85 + 1.17) A / 0.9 ≈ 22 W, which is ≈2.0 A from the 11.1 V pack. Adding the motor's 1.6 A gives **≈3.6 A worst case**. The 2200 mAh pack would last over 35 minutes even at that worst case, against a 3-minute round, so **capacity is not the constraint. Voltage is.** A freshly charged pack makes the motor ~17% stronger in low-PWM maneuvers ([ERR-11](docs/engineering-log.md#err-11--a-fresh-battery-over-rotates-the-dodges)), so we race inside an 11.70–12.15 V window.

**Heat.** At its typical 1.8 A, regulator #1 loses about 1 W at 90% efficiency. It is mounted in the airflow of the Pi on top of the car.

**Check before every session:** `vcgencmd get_throttled` must read `0x0` under full vision load.

### 3.2 Sensor selection and placement

| Sensor | Purpose | Placement | Notes |
|---|---|---|---|
| Raspberry Pi Camera Module V2 | Lane, corner-line and pillar detection | Front-center, ~20° downward tilt | Main vision system, OpenCV on the Pi |
| HC-SR04 (left) | Left wall distance | Left side of the chassis | Feeds the wall-centering PID |
| HC-SR04 (right) | Right wall distance | Right side of the chassis | Feeds the wall-centering PID |
| HC-SR04 (front) | Distance to the wall ahead when approaching a corner | Front bumper, facing forward | Obstacle round only — triggers the CRUCERO → MANIOBRA sequence |
| MPU-6050 *(v1)* | Heading integration during cornering and recovery | Center of chassis | Gyro Z integrated into `anguloGyro`, echoed back to the Pi |
| BNO085 *(v2, in integration)* | Fused heading at 100 Hz | Center of chassis, near the rotation axis | Replaces the MPU-6050; heading computed on the sensor |
| VL53L1X ToF ×4 *(v2, in integration)* | Near-field distance (≤ ~80 cm) with a software-set field of view | Front, left, right and rear, ~50 mm high | Cross-checked against the HC-SR04 — see [Why both](#why-both-ultrasonic-and-tof) |

#### Camera system

The camera handles lane geometry (via a bird's-eye-view transform), the orange corner-line markers, and red/green pillar detection. Image processing runs on the Raspberry Pi (Pi 4 → Pi 5 in v2) with OpenCV in real time and drives the Pure Pursuit planner.

It is mounted front-center with a ~20° downward tilt. We tested a horizontal mount first, but that captured too much background, which slowed detection and added noise. Tilting it down focuses the field of view on the track and the obstacle zone, which cut both false positives and computational load. The exact tilt is baked into the bird's-eye-view homography during calibration (see §4.3), so the mount must not move after calibration.

The lens is a wide-angle **NoIR** unit (~120° FOV), chosen over the original ~63° lens so the camera sees far enough ahead to react to a pillar and read the corner on the same frame. The wide lens ships without an IR-cut filter, which gave the raw image a heavy red cast and broke every HSV mask. The libcamera capture pipeline pins white-balance instead of letting it float — `libcamerasrc awb-enable=false colour-gains=<1.2,1.5>` — so the correction holds across venue lighting, and the pillar HSV ranges were re-tuned on the corrected image (see [ERR-03](#err-03--wide-angle-noir-lens-put-a-red-cast-on-every-frame)).

**v2 (Raspberry Pi 5):** fixed gains alone are not enough. The lens also needs its own **lens-shading table** (ALSC), otherwise the edges of the frame turn magenta. We calibrate that table from photos of a white sheet with the official Raspberry Pi tuning tool and ship it as a project tuning file, [`src/RASPI/cam/camera_tuning/`](src/RASPI/cam/camera_tuning/README.md). Result on a white sheet: R/G and B/G = 1.00 at the center **and** at all four corners (they were 1.3–1.4 at the corners).

#### HC-SR04 ultrasonic sensors

The left and right sensors drive lateral positioning and wall following. The **front** sensor was added for the Obstacle Challenge: because that round uses a segmented, stop-and-maneuver turn instead of a continuous arc (see §4.5), the car needs to know how far it is from the wall ahead so it can decide *when* to stop cruising and *which* maneuver (forward arc or reverse pivot) to run.

We originally tested VL53L0X time-of-flight sensors. On paper they win — ±3 mm accuracy versus ±15 mm for the HC-SR04, and a narrower beam. In practice, the black competition walls absorbed their 940 nm IR signal and consistently returned out-of-range readings at 300 mm. The HC-SR04 reflects off any surface regardless of color. We went with reliability over precision and made up the accuracy difference with software filtering (EMA on all three channels, plus a 5-sample median on the front channel to reject spikes before they can trigger a maneuver).

#### MPU-6050 IMU

The MPU-6050 gives heading and rotation data during cornering and recovery. The gyro Z axis is integrated each loop into `anguloGyro`, with a 1°/s deadband to suppress MEMS thermal drift on straights. On startup the firmware averages several hundred stationary samples to compute the gyro bias (`calcGyroOffsets`); if that offset comes back unusually large the firmware halves the integration scale as a safety net. The integrated heading is also sent back to the Pi in every acknowledgement so the vision side can dead-reckon obstacle positions (see §4.4).

#### BNO085 IMU (v2, in integration)

**Why replace the MPU-6050.** The MPU-6050 only gives a gyro *rate*. The ESP32 integrates it once per main loop, with a 1°/s deadband and a bias measured at boot. Our logs show what that costs:
- The integrated heading over a full run came out **6.5% low**: ≈1010° for the 1080° of 12 corners ([§6.3](#63-validation-matrix) #6).
- After every corner maneuver the heading carried a constant **−7.5° ± 0.9°** bias ([ERR-23](docs/engineering-log.md#err-23--systematic-heading-offset-after-every-corner)).
- The integration accuracy depends on how regular the main loop is, and the loop is busy with sensors and serial traffic.

The **BNO085** is a 9-axis sensor (gyroscope, accelerometer and magnetometer) that runs the sensor fusion on its own processor, with continuous bias calibration, and outputs a finished heading.

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
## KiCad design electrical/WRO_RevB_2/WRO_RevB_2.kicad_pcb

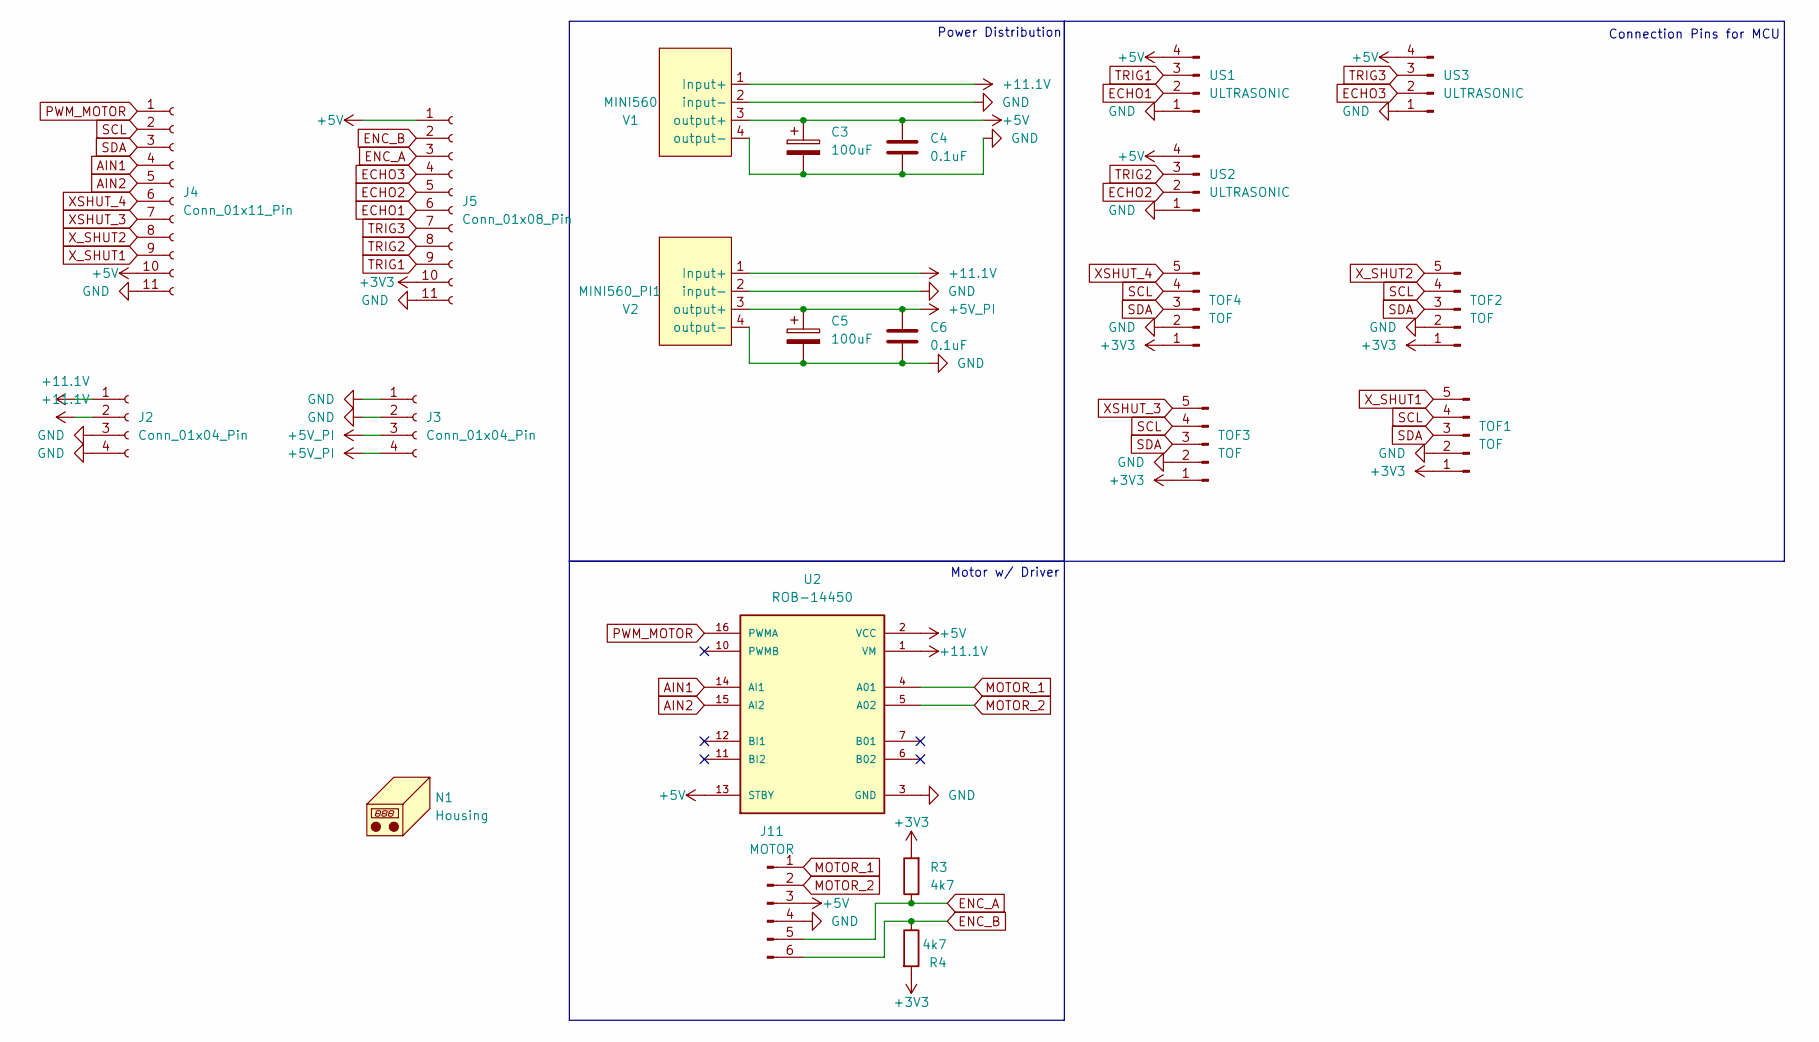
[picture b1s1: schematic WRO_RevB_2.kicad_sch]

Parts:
C3, C5: 100uF; CP_Radial_D5.0mm_P2.00mm
C4, C6: 0.1uF; C_Disc_D7.5mm_W2.5mm_P5.00mm
J2, J3: Conn_01x04_Pin; PinSocket_1x04_P2.54mm_Vertical
J4: Conn_01x11_Pin; PinSocket_1x11_P2.54mm_Vertical
J5: Conn_01x08_Pin; PinSocket_1x11_P2.54mm_Vertical
J11: MOTOR; JST_ZH_B6B-ZR_1x06_P1.50mm_Vertical
MINI560: V1; Mini560
MINI560_PI1: V2; Mini560
N1: Housing; KiCad-Logo2_12mm_SilkScreen
R3, R4: 4k7; R_1206_3216Metric_Pad1.30x1.75mm_HandSolder
TOF1, TOF2, TOF3, TOF4: TOF; JST_ZH_B5B-ZR_1x05_P1.50mm_Vertical
U2: ROB-14450; MODULE_ROB-14450; PARTREV 11-13-17
US1, US2, US3: ULTRASONIC; JST_ZH_B4B-ZR_1x04_P1.50mm_Vertical

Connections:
+3V3: J5.10, R3.2, R4.2, TOF1.1, TOF2.1, TOF3.1, TOF4.1
+5V: C3.1, C4.1, J4.10, J5.1, J11.3, MINI560.3 (output+), U2.2 (VCC), U2.13 (STBY), US1.4, US2.4, US3.4
+5V_PI: C5.1, C6.1, J3.3, J3.4, MINI560_PI1.3 (output+)
+11.1V: J2.1, J2.2, MINI560.1 (Input+), MINI560_PI1.1 (Input+), U2.1 (VM)
AIN1: J4.4, U2.14 (AI1)
AIN2: J4.5, U2.15 (AI2)
ECHO1: J5.6, US1.2
ECHO2: J5.5, US2.2
ECHO3: J5.4, US3.2
ENC_A: J5.3, J11.5, R3.1
ENC_B: J5.2, J11.6, R4.1
GND: C3.2, C4.2, C5.2, C6.2, J2.3, J2.4, J3.1, J3.2, J4.11, J5.11, J11.4, MINI560.2 (input-), MINI560.4 (output-), MINI560_PI1.2 (input-), MINI560_PI1.4 (output-), TOF1.2, TOF2.2, TOF3.2, TOF4.2, U2.3 (GND), U2.8 (GND), U2.9 (GND), US1.1, US2.1, US3.1
MOTOR_1: J11.1, U2.4 (A01)
MOTOR_2: J11.2, U2.5 (A02)
PWM_MOTOR: J4.1, U2.16 (PWMA)
SCL: J4.2, TOF1.4, TOF2.4, TOF3.4, TOF4.4
SDA: J4.3, TOF1.3, TOF2.3, TOF3.3, TOF4.3
TRIG1: J5.9, US1.3
TRIG2: J5.8, US2.3
TRIG3: J5.7, US3.3
XSHUT_3: J4.7, TOF3.5
XSHUT_4: J4.6, TOF4.5
X_SHUT1: J4.9, TOF1.5
X_SHUT2: J4.8, TOF2.5

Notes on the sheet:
Power Distribution
Motor w/ Driver
Connection Pins for MCU

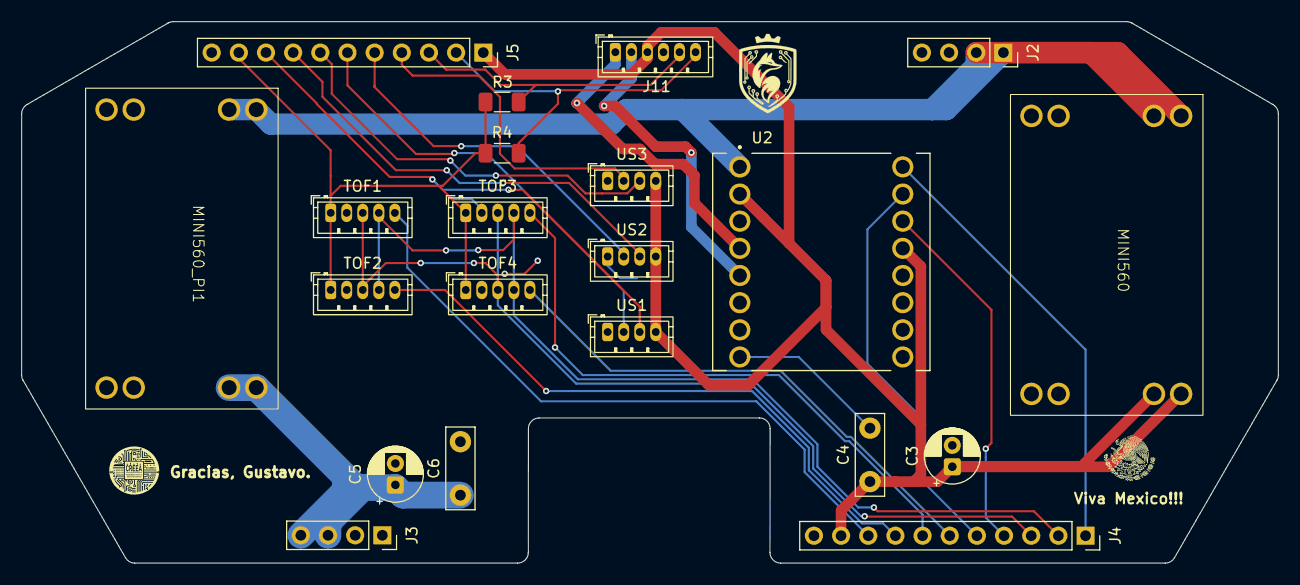
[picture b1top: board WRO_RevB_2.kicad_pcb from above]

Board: 2 copper layers, 117.5 x 50.6 mm, 22 parts (0 on the bottom side), 24 nets.

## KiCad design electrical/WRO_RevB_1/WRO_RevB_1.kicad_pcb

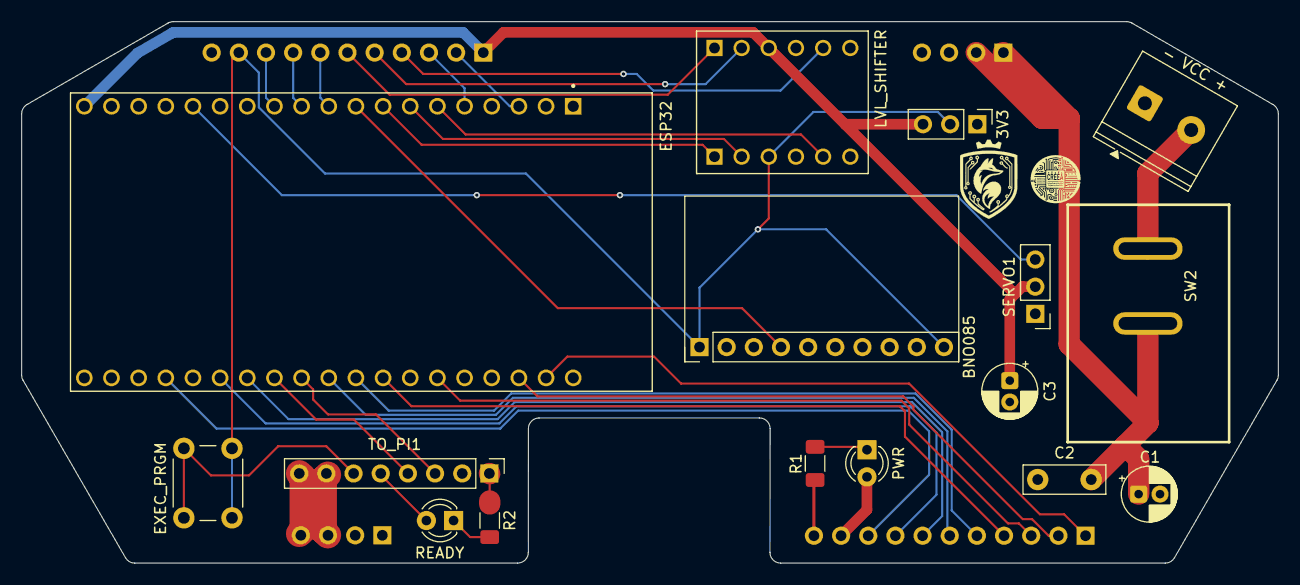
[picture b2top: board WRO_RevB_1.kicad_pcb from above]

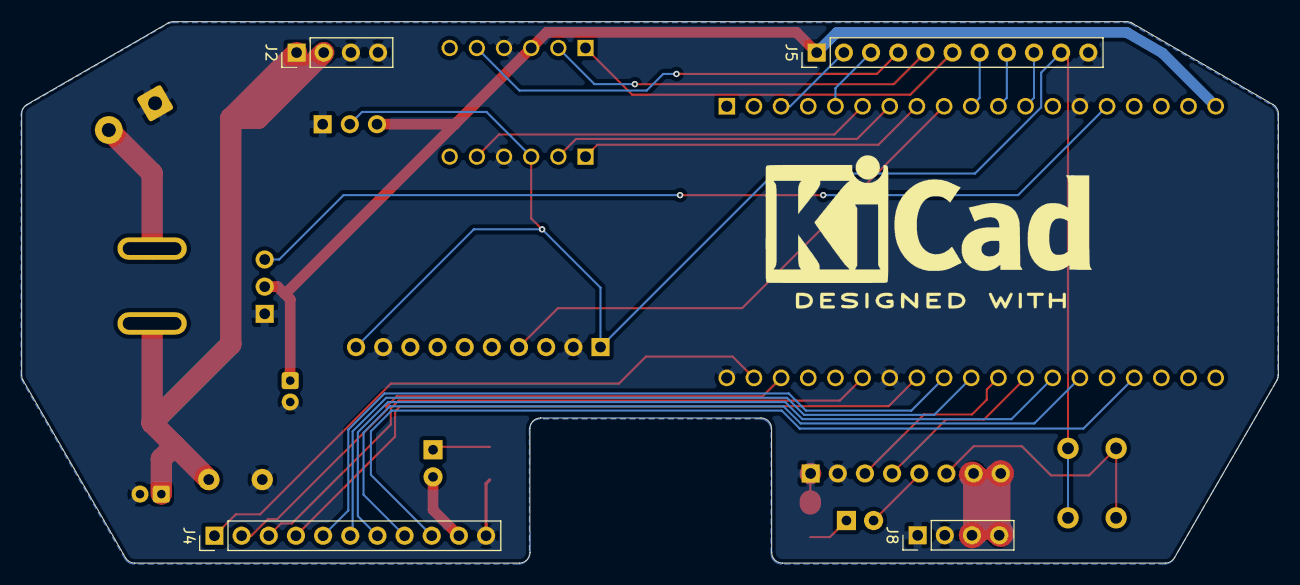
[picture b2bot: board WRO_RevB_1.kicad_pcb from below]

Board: 2 copper layers, 117.5 x 50.6 mm, 20 parts (4 on the bottom side), 34 nets.

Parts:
3V3: 3v3; PinHeader_1x03_P2.54mm_Vertical
- VCC +: VCC; TerminalBlock_Phoenix_PT-1,5-2-5.0-H_1x02_P5.00mm_Horizontal
BNO085: BNO085; PinHeader_1x10_P2.54mm_Vertical
C1: 470uF; CP_Radial_D5.0mm_P2.00mm
C2: 0.1uF; C_Disc_D7.5mm_W2.5mm_P5.00mm
C3: 1000uF; CP_Radial_D5.0mm_P2.00mm
ESP32: ESP32-DEVKITC-32D
EXEC_PRGM: EXEC_PRGM; SW_PUSH_6mm
J2, J8: Conn_01x04_Pin; PinHeader_1x04_P2.54mm_Vertical
J4, J5: Conn_01x11_Pin; PinHeader_1x11_P2.54mm_Vertical
LVL_SHIFTER: BOB-12009; CONV_BOB-12009
PWR: PWR; LED_D3.0mm
R1, R2: 330; R_1206_3216Metric_Pad1.30x1.75mm_HandSolder
READY: READY; LED_D3.0mm
SERVO1: SERVO; PinHeader_1x03_P2.54mm_Vertical
SW2: PWR; SW-TH_L22.2-W15.0-P7.00_KCD1-2P-P
TO_PI1: TO_PI; PinHeader_1x08_P2.54mm_Vertical

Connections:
+3V3: 3V3.2, BNO085.1, BNO085.10, EXEC_PRGM.1 (A), J5.10, LVL_SHIFTER.LV
+5V: 3V3.3, C3.1, ESP32.J2-19 (EXT_5V), J4.10, J5.1, LVL_SHIFTER.HV, PWR.2 (A), SERVO1.2
+5V_PI: J8.3, J8.4, TO_PI1.7, TO_PI1.8
+11.2V: C1.1, C2.2, J2.1, J2.2, SW2.2
AIN1: ESP32.J3-8 (IO19), J4.4
AIN2: ESP32.J3-9 (IO18), J4.5
BNO_RX: BNO085.4, ESP32.J2-9 (IO25)
ECHO1: J5.6, LVL_SHIFTER.HV1
ECHO1_L: ESP32.J2-8 (IO33), LVL_SHIFTER.LV1
ECHO2: J5.5, LVL_SHIFTER.HV2
ECHO2_L: ESP32.J2-7 (IO32), LVL_SHIFTER.LV2
ECHO3: J5.4, LVL_SHIFTER.HV3
ECHO3_L: ESP32.J2-6 (IO35), LVL_SHIFTER.LV3
ENC_A: ESP32.J2-5 (IO34), J5.3
ENC_B: ESP32.J2-3 (SENSOR_VP), J5.2
GND: 3V3.1, - VCC +.1, BNO085.2, BNO085.9, C1.2, C2.1, C3.2, ESP32.J2-14 (GND1), ESP32.J3-1 (GND3), ESP32.J3-7 (GND2), J2.3, J2.4, J4.11, J5.11, J8.1, J8.2, LVL_SHIFTER.GND_1 (GND), LVL_SHIFTER.GND_2 (GND), R1.2, R2.2, SERVO1.1, TO_PI1.1, TO_PI1.2
unnamed: PWR.1 (K), R1.1
unnamed: R2.1, READY.1 (K)
unnamed: - VCC +.2, SW2.1
PRGM: EXEC_PRGM.2 (B), TO_PI1.6
PWM_MOTOR: ESP32.J3-2 (IO23), J4.1
READY: READY.2 (A), TO_PI1.5
RX: ESP32.J3-12 (IO16), TO_PI1.4
SCL: ESP32.J3-3 (IO22), J4.2
SDA: ESP32.J3-6 (IO21), J4.3
SERVO: ESP32.J2-15 (IO13), SERVO1.3
TRIG1: ESP32.J2-12 (IO14), J5.9
TRIG2: ESP32.J2-11 (IO27), J5.8
TRIG3: ESP32.J2-10 (IO26), J5.7
TX: ESP32.J3-11 (IO17), TO_PI1.3
XSHUT_3: ESP32.J3-13 (IO4), J4.7
XSHUT_4: ESP32.J3-10 (IO5), J4.6
X_SHUT1: ESP32.J3-16 (IO15), J4.9
X_SHUT2: ESP32.J3-14 (IO0), J4.8

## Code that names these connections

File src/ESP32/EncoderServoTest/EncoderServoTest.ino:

/*
 * EncoderServoTest — aísla por qué el encoder cuenta de menos cuando el servo
 * se mueve. Con la llanta EN EL AIRE, al prenderse espera 2 s, pone el motor
 * a PWM fijo y corre 3 fases de 4 s:
 *   A) servo quieto en el centro
 *   B) servo moviéndose (centro ±20, cambia cada 100 ms)
 *   C) servo quieto otra vez
 * El encoder se cuenta DOS veces a la vez, con los mismos pines:
 *   ISR  = interrupciones + tabla de cuadratura (como RectaBnoTest)
 *   PCNT = contador por hardware del ESP32, con filtro de glitches de 1 us
 * Al final imprime una tabla con las cuentas por segundo de cada fase.
 * Monitor a 115200.
 *
 * Cómo leerla (el motor va al mismo PWM en las 3 fases):
 *   - ISR baja en B pero PCNT no      -> problema de software de la ISR -> usar PCNT
 *   - ISR y PCNT bajan igual en B, con
 *     "atras" ~0 y pocos errores      -> el motor de verdad va más lento (el 5V
 *                                         del servo afecta al driver)
 *   - ISR baja en B con muchos "atras"
 *     o errores                       -> la señal del encoder llega sucia (eléctrico)
 *   - Nada baja en B                  -> el servo no es el problema
 *
 * PINES: driver PWMA=23, AIN1=18, AIN2=19 | servo 13 | encoder A=34, B=36
 */

#include "driver/pulse_cnt.h"

const int PWMA = 23;
const int A1   = 18;
const int A2   = 19;
const int SERVO_PIN = 13;
const int ENC_A = 34;
const int ENC_B = 36;

const int PWM_PRUEBA   = 80;
int       centroServo  = 75;
const int SERVO_AMPLITUD = 20;
const uint32_t FASE_MS = 4000;

// ---------------- Conteo por ISR (igual que los otros sketches) ----------------
const int8_t TABLA[16] = {  0, -1, +1,  2,
                           +1,  0,  2, -1,
                           -1,  2,  0, +1,
                            2, +1, -1,  0 };
volatile int32_t  cuenta = 0;
volatile uint32_t errores = 0, pasosMas = 0, pasosMenos = 0;
volatile uint8_t  estado = 0;
portMUX_TYPE mux = portMUX_INITIALIZER_UNLOCKED;

void IRAM_ATTR isrEncoder() {
  uint8_t nuevo = (digitalRead(ENC_A) << 1) | digitalRead(ENC_B);
  portENTER_CRITICAL_ISR(&mux);
  int8_t paso = TABLA[(estado << 2) | nuevo];
  if (paso == 2) errores++;
  else {
    cuenta += paso;
    if (paso > 0) pasosMas++;
    else if (paso < 0) pasosMenos++;
  }
  estado = nuevo;
  portEXIT_CRITICAL_ISR(&mux);
}

// ---------------- Conteo por hardware (PCNT, x4) ----------------
pcnt_unit_handle_t pcnt = NULL;

bool iniciarPcnt() {
  pcnt_unit_config_t ucfg = {};
  ucfg.low_limit  = -30000;
  ucfg.high_limit =  30000;
  ucfg.flags.accum_count = 1;          // acumula al desbordar los límites
  if (pcnt_new_unit(&ucfg, &pcnt) != ESP_OK) return false;

  pcnt_glitch_filter_config_t fcfg = {};
  fcfg.max_glitch_ns = 1000;           // ignora pulsos de menos de 1 us
  pcnt_unit_set_glitch_filter(pcnt, &fcfg);

  pcnt_chan_config_t cfgA = {};
  cfgA.edge_gpio_num  = ENC_A;
  cfgA.level_gpio_num = ENC_B;
  pcnt_channel_handle_t chA;
  pcnt_new_channel(pcnt, &cfgA, &chA);

  pcnt_chan_config_t cfgB = {};
  cfgB.edge_gpio_num  = ENC_B;
  cfgB.level_gpio_num = ENC_A;
  pcnt_channel_handle_t chB;
  pcnt_new_channel(pcnt, &cfgB, &chB);

  // Decodificación x4 (la del ejemplo rotary_encoder de ESP-IDF).
  pcnt_channel_set_edge_action(chA, PCNT_CHANNEL_EDGE_ACTION_DECREASE, PCNT_CHANNEL_EDGE_ACTION_INCREASE);
  pcnt_channel_set_level_action(chA, PCNT_CHANNEL_LEVEL_ACTION_KEEP, PCNT_CHANNEL_LEVEL_ACTION_INVERSE);
  pcnt_channel_set_edge_action(chB, PCNT_CHANNEL_EDGE_ACTION_INCREASE, PCNT_CHANNEL_EDGE_ACTION_DECREASE);
  pcnt_channel_set_level_action(chB, PCNT_CHANNEL_LEVEL_ACTION_KEEP, PCNT_CHANNEL_LEVEL_ACTION_INVERSE);

  pcnt_unit_add_watch_point(pcnt, ucfg.high_limit);
  pcnt_unit_add_watch_point(pcnt, ucfg.low_limit);
  pcnt_unit_enable(pcnt);
  pcnt_unit_clear_count(pcnt);
  pcnt_unit_start(pcnt);
  return true;
}

int32_t leePcnt() {
  int v = 0;
  pcnt_unit_get_count(pcnt, &v);
  return v;
}

// ---------------- Servo ----------------
void escribirServo(int angulo) {
  angulo = constrain(angulo, 2, 154);
  int pulso = map(angulo, 0, 180, 500, 2500);
  ledcWrite(SERVO_PIN, (pulso * ((1 << 16) - 1)) / 20000);
}

// ---------------- Fases ----------------
struct Medida {
  int32_t  isr, pcnt;
  uint32_t mas, menos, err;
};

const char* NOMBRES[3] = {"A servo quieto  ", "B servo moviendo", "C servo quieto  "};
Medida ini[3], fin[3];
bool  terminado = false;

// Sin el tipo Medida en la firma: el IDE de Arduino declara las funciones
// arriba de todo, antes del struct, y no lo encontraría.
void foto(int f, bool esFin) {
  Medida& m = esFin ? fin[f] : ini[f];
  portENTER_CRITICAL(&mux);
  m.isr = cuenta; m.mas = pasosMas; m.menos = pasosMenos; m.err = errores;
  portEXIT_CRITICAL(&mux);
  m.pcnt = leePcnt();
}

void correrFase(int f) {
  foto(f, false);
  uint32_t t0 = millis(), tServo = 0;
  bool lado = false;
  while (millis() - t0 < FASE_MS) {
    if (f == 1 && millis() - tServo >= 100) {
      tServo = millis();
      lado = !lado;
      escribirServo(centroServo + (lado ? SERVO_AMPLITUD : -SERVO_AMPLITUD));
    }
    delay(1);
  }
  if (f == 1) escribirServo(centroServo);
  foto(f, true);
}

void imprimirTabla() {
  Serial.println("fase               ISR/s   PCNT/s   pasos atras   errores");
  for (int f = 0; f < 3; f++) {
    float s = FASE_MS / 1000.0f;
    Serial.printf("%s  %7.0f  %7.0f   %11lu   %7lu\n", NOMBRES[f],
                  abs(fin[f].isr - ini[f].isr) / s, abs(fin[f].pcnt - ini[f].pcnt) / s,
                  // con la llanta siempre hacia adelante, "atras" son los pasos del sentido minoritario
                  (unsigned long)min(fin[f].mas - ini[f].mas, fin[f].menos - ini[f].menos),
                  (unsigned long)(fin[f].err - ini[f].err));
  }
  Serial.println();
}

void setup() {
  Serial.begin(115200);
  delay(500);

  // PCNT primero: su configuración de pines apaga las interrupciones GPIO,
  // y attachInterrupt de abajo las vuelve a prender.
  if (!iniciarPcnt()) Serial.println("PCNT no arrancó");

  pinMode(ENC_A, INPUT);
  pinMode(ENC_B, INPUT);
  estado = (digitalRead(ENC_A) << 1) | digitalRead(ENC_B);
  attachInterrupt(digitalPinToInterrupt(ENC_A), isrEncoder, CHANGE);
  attachInterrupt(digitalPinToInterrupt(ENC_B), isrEncoder, CHANGE);

  pinMode(A1, OUTPUT); pinMode(A2, OUTPUT);
  digitalWrite(A1, LOW); digitalWrite(A2, LOW);
  ledcAttach(PWMA, 1000, 8);
  ledcWrite(PWMA, 0);
  ledcAttach(SERVO_PIN, 50, 16);
  escribirServo(centroServo);

  Serial.println("EncoderServoTest: llanta EN EL AIRE. Arranca en 2 s...");
  delay(2000);

  digitalWrite(A1, HIGH); digitalWrite(A2, LOW);
  ledcWrite(PWMA, PWM_PRUEBA);
  delay(1000);   // que el motor llegue a su velocidad

  for (int f = 0; f < 3; f++) {
    Serial.printf("fase %s...\n", NOMBRES[f]);
    correrFase(f);
  }

  ledcWrite(PWMA, 0);
  digitalWrite(A1, LOW); digitalWrite(A2, LOW);
  terminado = true;
  imprimirTabla();
}

void loop() {
  static uint32_t t = 0;
  if (terminado && millis() - t >= 3000) {
    t = millis();
    imprimirTabla();
  }
}

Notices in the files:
README.md:
License:
Released under the [MIT License](LICENSE) — free to use, modify and build on, code and documentation alike, with attribution.
This repository is public as required by WRO Future Engineers rules and will remain public for at least 12 months after the competition.
WRO Future Engineers 2026 — FoxRobotics — México
